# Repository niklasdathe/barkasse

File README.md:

# Barkasse Sensor Infrastructure

A simple, easy-to-extend sensor for the Barkasse project.

## 1. Hub

This section describes the setup and structure of the on board hub.

### 1.1 Core Ideas
- Sensor nodes (ESP32/Arduino) publish JSON over MQTT via Ethernet/PoE or WiFi.
- A Raspberry Pi / reTerminal acts as a central hub with Mosquitto + Node-RED (HTTP/WebSocket) serving a static UI.
- The UI auto-discovers new sensors and displays them live on a 10-inch touch panel.

### 1.2 MQTT Topics & JSON Schema
- Topic: `barkasse/<node>/<cluster>/<sensor>`
- Payload:
  ```json
  {
  "node": "esp32p4-01",
  "cluster": "weather",
  "sensor": "temperature",
  "value": 22.4,
  "unit": "°C",
  "ts": "2025-10-10T12:00:00Z"
  }
  ```
### 1.3 Directory Overview

| Folder                  | Description                                            |
| ----------------------- | ------------------------------------------------------ |
| `example-sensor-implementations/esp32p4-weatherstation-mock`  | ESP32-P4 (Ethernet) demo publishing weather data |
| `example-sensor-implementations/esp32-wroom-waterstation-mock`| ESP32 WROOM (WiFi) demo publishing water data    |
| `mosquitto/`            | Mosquitto config for native install                    |
| `nodered_data/`         | Node-RED userDir (flows + settings)                    |
| `ui/`                   | Static touchscreen UI                                  |
| `systemd/`              | System services for hub + fullscreen UI                |

### 1.4 Setup on Raspberry Pi

This repo is designed to run **without Docker**.

**1. Install Mosquitto + Node-RED**
```bash
sudo apt update
sudo apt install -y mosquitto mosquitto-clients
```

Install Node-RED (if not already present):
```bash
bash <(curl -sL https://raw.githubusercontent.com/node-red/linux-installers/master/deb/update-nodejs-and-nodered)
```

**2. Configure Mosquitto**
```bash
sudo cp mosquitto/mosquitto.conf /etc/mosquitto/conf.d/barkasse.conf
sudo systemctl enable --now mosquitto
```

**3. Enable services**
```bash
sudo cp systemd/barkasse-ui.service /etc/systemd/system/
sudo systemctl daemon-reload
sudo systemctl enable --now barkasse-ui.service
```

The UI is served at http://localhost:8080.

### 1.5 Isolated LAN (hub assigns IPs + NTP)

If the hub and ESP32 are the only devices on a switch, the hub must provide IP addresses.

This repo includes a small coordinator setup that configures:

- Static IP on `eth0` (default `192.168.10.10/24`)
- DHCP (dnsmasq) so the ESP32 gets an IP when plugged in
- NTP (chrony) served by the hub

Run:

```bash
chmod +x scripts/setup-lan-coordinator.sh scripts/barkasse-dhcp-mqtt-hook.sh
BARKASSE_LAN_IFACE=eth0 BARKASSE_LAN_IP=192.168.10.10 ./scripts/setup-lan-coordinator.sh
```

Details: see [docs/lan_coordinator.md](docs/lan_coordinator.md).

### 1.5 Implementation Examples

- **ESP32-P4 Weather (Ethernet)** (See `example-sensor-implementations/esp32p4-weatherstation-mock`)

- **ESP32 WROOM Water (WiFi)** (See `example-sensor-implementations/esp32-wroom-waterstation-mock`)

- **(LoRa)** TODO

### 1.6 Extend
Add any new sensor/cluster by publishing to the topic contract. No UI edits required.

### 1.7 Maintenance

- Check backend: systemctl status barkasse-ui.service
- Check browser: systemctl status barkasse-fullscreen.service
- Update manually: git pull && sudo systemctl restart barkasse-ui barkasse-fullscreen

### 1.8 UI menu (clear history & fullscreen)

The hub keeps recent datapoints in memory to render charts. You can delete this local history if needed:

- UI: Use the top-right menu (⋮) and choose "Clear history". All stored series are removed.
- API: Send a POST request to the hub:
  - Clear everything: POST /history/clear
  - Clear one series: POST /history/clear?key=<node>/<cluster>/<sensor>

This only affects the in-memory cache on the Pi; live updates continue as new datapoints arrive.

This setup does not require Chromium at all. If you want the UI to open automatically on boot
in fullscreen, enable `systemd/barkasse-fullscreen.service`.

## 2. Server

This section describes the setup and structure of the server side.  

| MQTT topic (barkasse/node)                               | node         | cluster     | sensor                 | unit     | What it means                                                                      | Source / where it comes from                                                |
| ----------------------------------------- | ------------ | ----------- | ---------------------- | -------- | ---------------------------------------------------------------------------------- | --------------------------------------------------------------------------- |
| `barkasse/esp32p4-01` | `esp32p4-01` | `weather`   | `temperature`          | `°C`     | Ambient/outside temperature (mock)                                                 | ESP32-P4 weather mock (`publishSensor("temperature", ...)`)                 |
| `barkasse/esp32p4-01`    | `esp32p4-01` | `weather`   | `humidity`             | `%`      | Relative humidity (mock)                                                           | ESP32-P4 weather mock                                                       |
| `barkasse/esp32p4-01`    | `esp32p4-01` | `weather`   | `pressure`             | `hPa`    | Air pressure (mock)                                                                | ESP32-P4 weather mock                                                       |
| `barkasse/esp32p4-01`  | `esp32p4-01` | `weather`   | `wind_speed`           | `m/s`    | Wind speed (mock)                                                                  | ESP32-P4 weather mock                                                       |
| `barkasse/esp32p4-01`    | `esp32p4-01` | `weather`   | `wind_dir`             | `°`      | Wind direction (0–360°) (mock)                                                     | ESP32-P4 weather mock                                                       |
| `barkasse/esp32p4-01`       | `esp32p4-01` | `weather`   | *(summary envelope)*   | —        | One JSON message containing **all weather sensors** under `sensors{...}`           | ESP32-P4 weather mock (`publishCluster()`)                                  |
| `barkasse/sensors`                        | `hub`        | `enclosure` | `temperature`          | `°C`     | Enclosure internal air temperature                                                 | Hub I2C script AM2301B (`am2301b_read.py` → MQTT Publish Enclosure)         |
| `barkasse/sensors`                        | `hub`        | `enclosure` | `humidity`             | `%`      | Enclosure internal relative humidity                                               | Hub I2C script AM2301B (`am2301b_read.py` → MQTT Publish Enclosure)         |
| `barkasse/sensors`                        | `hub`        | `enclosure` | `surface_temp`         | `°C`     | Estimated “cold surface” temperature inside enclosure (used for condensation risk) | Node-RED “Condensation Risk” flow: `T_surface = (T_inside + T_outside)/2`   |
| `barkasse/sensors`                        | `hub`        | `enclosure` | `dew_point`            | `°C`     | Dew point temperature computed from inside T + RH (Magnus formula)                 | Node-RED “Condensation Risk” flow                                           |
| `barkasse/sensors`                        | `hub`        | `enclosure` | `condensation_delta`   | `°C`     | `dew_point - surface_temp` (positive ⇒ condensation likely)                        | Node-RED “Condensation Risk” flow                                           |
| `barkasse/sensors`                        | `hub`        | `enclosure` | `condensation_risk`    | `%`      | Risk mapped from `condensation_delta` using linear low/high thresholds             | Node-RED “Condensation Risk” flow (`risk_low_delta_c`, `risk_high_delta_c`) |
| `barkasse/sensors`                        | `hub`        | `enclosure` | `condensation`         | *(none)* | Boolean flag: `1` if `surface_temp <= dew_point`, else `0`                         | Node-RED “Condensation Risk” flow                                           |
| `barkasse/sensors`                        | `hub`        | `gnss`      | `fix_valid`            | *(none)* | RMC validity (A=1 / V=0)                                                           | Node-RED GNSS parser (EC25 NMEA → JSON)                                     |
| `barkasse/sensors`                        | `hub`        | `gnss`      | `fix_quality`          | *(none)* | GGA fix quality (0=no fix, 1=GPS, 2=DGPS, …)                                       | Node-RED GNSS parser (from GGA)                                             |
| `barkasse/sensors`                        | `hub`        | `gnss`      | `fix_type`             | *(none)* | GSA fix type (1=no fix, 2=2D, 3=3D)                                                | Node-RED GNSS parser (from GSA)                                             |
| `barkasse/sensors`                        | `hub`        | `gnss`      | `sats_used`            | *(none)* | Satellites used in solution                                                        | Node-RED GNSS parser (from GGA)                                             |
| `barkasse/sensors`                        | `hub`        | `gnss`      | `hdop`                 | *(none)* | Horizontal dilution of precision                                                   | Node-RED GNSS parser (GGA/GSA)                                              |
| `barkasse/sensors`                        | `hub`        | `gnss`      | `pdop`                 | *(none)* | Position dilution of precision                                                     | Node-RED GNSS parser (from GSA)                                             |
| `barkasse/sensors`                        | `hub`        | `gnss`      | `vdop`                 | *(none)* | Vertical dilution of precision                                                     | Node-RED GNSS parser (from GSA)                                             |
| `barkasse/sensors`                        | `hub`        | `gnss`      | `lat`                  | `deg`    | Latitude in decimal degrees                                                        | Node-RED GNSS parser (RMC/GGA)                                              |
| `barkasse/sensors`                        | `hub`        | `gnss`      | `lon`                  | `deg`    | Longitude in decimal degrees                                                       | Node-RED GNSS parser (RMC/GGA)                                              |
| `barkasse/sensors`                        | `hub`        | `gnss`      | `alt`                  | `m`      | Altitude above mean sea level                                                      | Node-RED GNSS parser (from GGA)                                             |
| `barkasse/sensors`                        | `hub`        | `gnss`      | `speed`                | `m/s`    | Ground speed (converted from knots if needed)                                      | Node-RED GNSS parser (RMC/VTG)                                              |
| `barkasse/sensors`                        | `hub`        | `gnss`      | `speed_kmh`            | `km/h`   | Ground speed in km/h                                                               | Node-RED GNSS parser (RMC/VTG)                                              |
| `barkasse/sensors`                        | `hub`        | `gnss`      | `course`               | `deg`    | Course over ground                                                                 | Node-RED GNSS parser (RMC/VTG)                                              |
| `barkasse/sensors`                        | `hub`        | `gnss`      | `gps_sats_in_view`     | *(none)* | GPS satellites in view (from GSV aggregation)                                      | Node-RED GNSS parser (GSV cycle)                                            |
| `barkasse/sensors`                        | `hub`        | `gnss`      | `gps_snr_avg`          | `dB`     | Average SNR of GPS sats in view                                                    | Node-RED GNSS parser (GSV cycle)                                            |
| `barkasse/sensors`                        | `hub`        | `gnss`      | `galileo_sats_in_view` | *(none)* | Galileo satellites in view (from GSV aggregation)                                  | Node-RED GNSS parser (GSV cycle)                                            |
| `barkasse/sensors`                        | `hub`        | `gnss`      | `galileo_snr_avg`      | `dB`     | Average SNR of Galileo sats in view                                                | Node-RED GNSS parser (GSV cycle)                                            |

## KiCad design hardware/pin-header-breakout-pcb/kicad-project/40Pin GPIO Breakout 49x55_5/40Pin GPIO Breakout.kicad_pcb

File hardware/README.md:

This folder holds the informations / files for the hardware components of the hub.

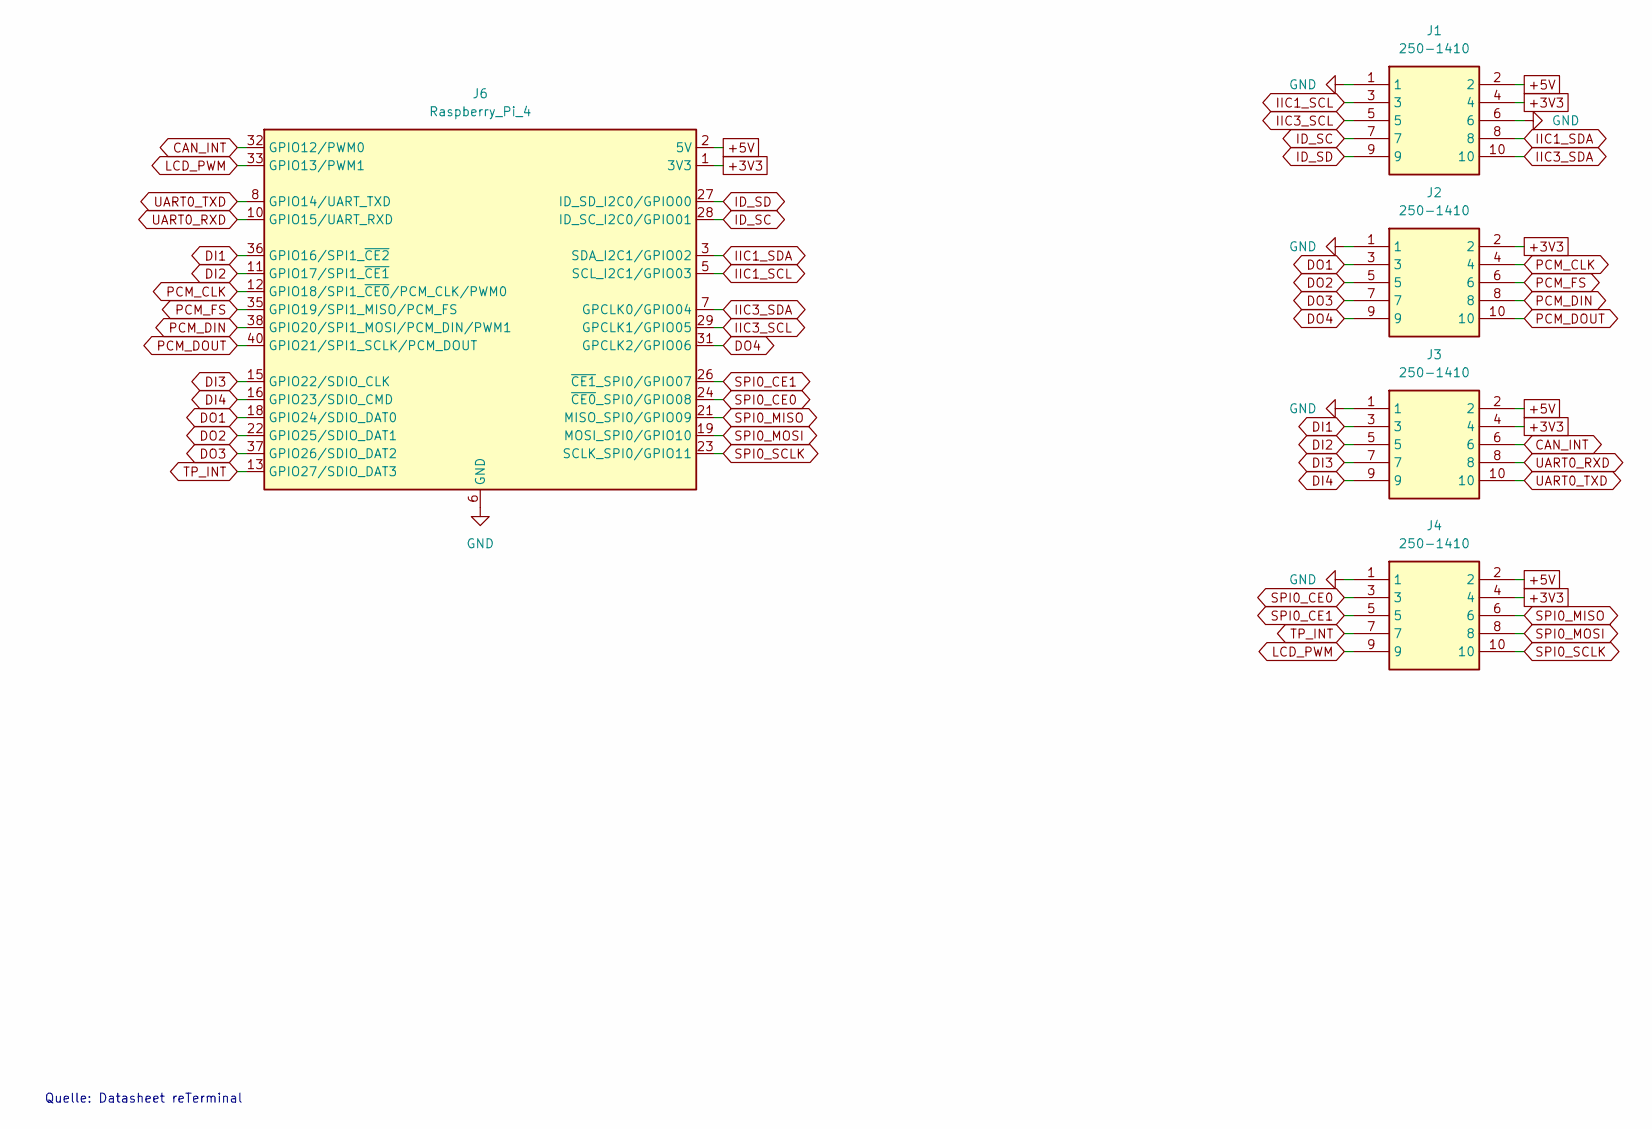
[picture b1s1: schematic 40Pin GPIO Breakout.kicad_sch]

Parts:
J1, J2, J3, J4: 250-1410; CONN10_250-1410_WAG; Manufacturer_Part_Number 250-1410
J6: Raspberry_Pi_4; PinHeader_2x20_P2.54mm_Vertical

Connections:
+3V3: J1.4, J2.2, J3.4, J4.4, J6.1 (3V3), J6.17 (3V3)
+5V: J1.2, J3.2, J4.2, J6.2 (5V), J6.4 (5V)
CAN_INT: J3.6, J6.32 (GPIO12/PWM0)
DI1: J3.3, J6.36 (GPIO16/SPI1_~CE2)
DI2: J3.5, J6.11 (GPIO17/SPI1_~CE1)
DI3: J3.7, J6.15 (GPIO22/SDIO_CLK)
DI4: J3.9, J6.16 (GPIO23/SDIO_CMD)
DO1: J2.3, J6.18 (GPIO24/SDIO_DAT0)
DO2: J2.5, J6.22 (GPIO25/SDIO_DAT1)
DO3: J2.7, J6.37 (GPIO26/SDIO_DAT2)
DO4: J2.9, J6.31 (GPCLK2/GPIO06)
GND: J1.1, J1.6, J2.1, J3.1, J4.1, J6.6 (GND), J6.9 (GND), J6.14 (GND), J6.20 (GND), J6.25 (GND), J6.30 (GND), J6.34 (GND), J6.39 (GND)
ID_SC: J1.7, J6.28 (ID_SC_I2C0/GPIO01)
ID_SD: J1.9, J6.27 (ID_SD_I2C0/GPIO00)
IIC1_SCL: J1.3, J6.5 (SCL_I2C1/GPIO03)
IIC1_SDA: J1.8, J6.3 (SDA_I2C1/GPIO02)
IIC3_SCL: J1.5, J6.29 (GPCLK1/GPIO05)
IIC3_SDA: J1.10, J6.7 (GPCLK0/GPIO04)
LCD_PWM: J4.9, J6.33 (GPIO13/PWM1)
PCM_CLK: J2.4, J6.12 (GPIO18/SPI1_~CE0/PCM_CLK/PWM0)
PCM_DIN: J2.8, J6.38 (GPIO20/SPI1_MOSI/PCM_DIN/PWM1)
PCM_DOUT: J2.10, J6.40 (GPIO21/SPI1_SCLK/PCM_DOUT)
PCM_FS: J2.6, J6.35 (GPIO19/SPI1_MISO/PCM_FS)
SPI0_CE0: J4.3, J6.24 (~CE0_SPI0/GPIO08)
SPI0_CE1: J4.5, J6.26 (~CE1_SPI0/GPIO07)
SPI0_MISO: J4.6, J6.21 (MISO_SPI0/GPIO09)
SPI0_MOSI: J4.8, J6.19 (MOSI_SPI0/GPIO10)
SPI0_SCLK: J4.10, J6.23 (SCLK_SPI0/GPIO11)
TP_INT: J4.7, J6.13 (GPIO27/SDIO_DAT3)
UART0_RXD: J3.8, J6.10 (GPIO15/UART_RXD)
UART0_TXD: J3.10, J6.8 (GPIO14/UART_TXD)

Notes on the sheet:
Quelle: Datasheet reTerminal

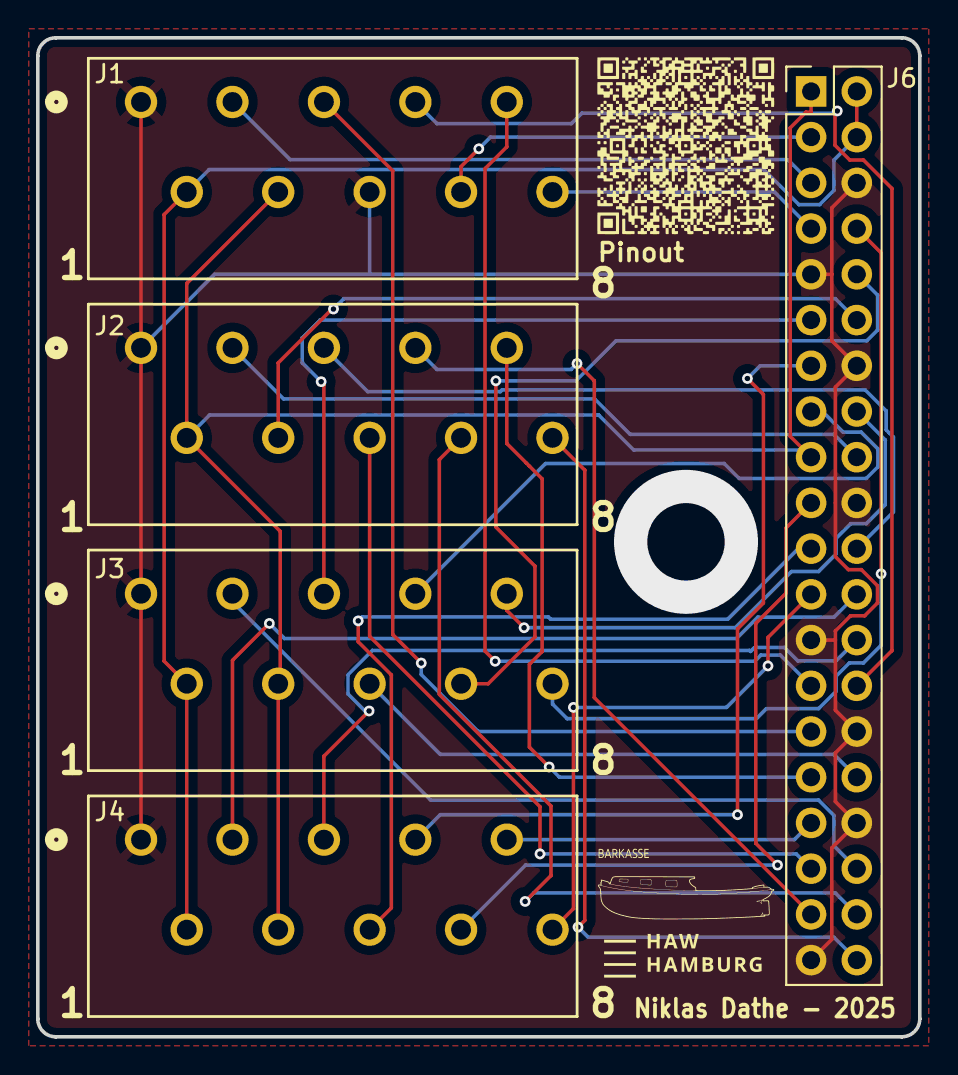
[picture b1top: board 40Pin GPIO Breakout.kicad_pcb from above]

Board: 2 copper layers, 49.0 x 55.5 mm, 5 parts (0 on the bottom side), 31 nets.

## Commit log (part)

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2025-10-09 Implement weather cluster emulation with MQTT
    This code emulates a weather cluster using an ESP32-P4, publishing temperature, humidity, pressure, and wind data via MQTT. It includes setup for Ethernet connectivity and JSON serialization for sens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
2025-10-09 Add Mosquitto configuration file
2025-10-09 Add FastAPI, Uvicorn, and Paho-MQTT dependencies
2025-10-09 Implement FastAPI with MQTT integration
2025-10-09 Add initial HTML structure for Barkasse Hub
2025-10-09 Add styles for layout and design in styles.css
2025-10-09 Rename pi/app/background.png to pi/app/static/background.png
2025-10-09 Revise README for folder structure and UI instructions
    Updated folder names and simplified UI startup instructions.
2025-10-09 Add systemd service for Chromium kiosk mode
2025-10-10 functioning commuication
2025-10-10 added aüpp.js with tile system
2025-10-10 Update styles.css
    Moved the tiles to reveal the subtitle of the background picture
2025-10-10 Increase top padding of main grid
2025-10-10 Add auto-git-update.service for automatic updates
    This service automatically updates the Barkasse project from GitHub when the network is online.
2025-10-10 Update service description and dependencies
2025-10-10 Relocate auto-git-update.service file
    Move auto-git-update.service to /etc/systemd/system.
2025-10-10 Refactor kiosk-chromium.service configuration
    Moved service file to /etc/systemd/system and updated ExecStart options for Chromium.
2025-10-10 Change service user and working directory for barkasse-ui
2025-10-10 Change user and update git pull logic in service
2025-10-10 Modify barkasse-ui.service for better execution
    Updated service file to run uvicorn with virtual environment activation and added group specification.
2025-10-10 Modify kiosk-chromium.service for Wayland and user settings
    Updated kiosk-chromium.service for Wayland support and improved environment variables.
2025-10-10 Update header to include 'DASHBOARD'
2025-10-10 Change title from 'BARKASSE DASHBOARD' to 'SENSOR-HUB'
2025-10-10 Enable drag-and-drop reordering for dashboard tiles
2025-10-10 Improve tile drag animations
2025-10-10 Revert "Improve tile drag animations"
2025-10-10 Revise README for clarity and additional details
    Updated README to enhance clarity and structure, including MQTT topics and JSON schema.
2025-10-10 Add maintenance section to README
    Added maintenance section with service checks and update instructions.
2025-10-10 Refactor app.js for tile management and charts
    Refactor app.js to enhance tile management and chart functionality. Added drag-and-drop support for tiles, improved WebSocket handling, and updated chart rendering logic.
2025-10-10 Enhance styles for layout and components
    Added styles for header, periods, chart section, and tile elements.
2025-10-10 Update index.html structure and add chart section
2025-10-10 Reorganize HTML structure for chart and tiles
2025-10-10 Enable droppable functionality for trash element
    Updated styles for the trash element to allow droppable functionality when visible.
2025-10-10 Enhance chart rendering and title management
    Updated chart rendering logic to handle cases with no data and improved chart title/hint management.
2025-10-10 Refactor timestamp handling and improve comments
2025-10-10 Reorganize HTML structure for better layout
2025-10-10 Refactor styles for layout and components
2025-10-10 Refactor app.js for improved readability and performance
    Refactor and optimize JavaScript code for better readability and performance. Includes improvements in WebSocket handling, tile rendering, and timestamp parsing.
2025-10-10 Refactor timestamp handling and update health dot logic
2025-10-10 Refactor periods styles and button appearance
    Updated styles for the periods class and buttons.
2025-10-10 Refactor cutoff logic and data initialization
2025-10-10 Refactor app.js for clarity and efficiency
    Refactor app.js to improve readability and maintainability by reorganizing functions, removing redundant code, and updating variable names.
2025-10-10 Refactor main.py for improved readability and structure
2025-10-10 Enhance timestamp handling in main.py for better accuracy and readability. Improved normalization logic for various timestamp formats and added fallback to current time on parsing failure.
2025-10-10 Implement NTP synchronization and time validation in main.ino. Added functions to check time validity and synchronize time via SNTP, ensuring accurate timestamps for data publishing.
2025-10-13 Refactor styles for header and chart tiles
2025-10-13 Refactor app.js to include HTML layout
    Replaced JavaScript code with HTML structure for the app.
2025-10-13 Refactor app.js to include helper functions and globals
2025-10-13 Add HTML structure for Barkasse Hub
2025-10-13 Enhance styles for floating action buttons and layout
    Added transition effects to floating action buttons and improved layout styles.
2025-10-13 Refactor app.js for improved readability and structure
2025-10-13 Refactor chart handling and drag-and-drop features
    Refactor chart handling and drag-and-drop functionality in app.js. Updated event listeners and improved chart rendering logic.
2025-10-13 Refactor index.html structure and remove duplicates
2025-10-13 Refactor styles for grid and button elements
2025-10-13 Add HTML structure and metadata to index.html
2025-10-13 Embed chart tile in grid and add graph creation dropzone
2025-10-13 Allow multiple concurrent graph tiles
2025-10-13 Revert "Allow multiple graphs and enforce half-width layout"
2025-10-13 Refactor graph tile logic for multi-instance support
    Refactor graph tile handling to support multiple instances and improve event management.
2025-10-13 Implement responsive grid layout for main section
    Added responsive grid layout for sensors and adjusted graph tile spans.
2025-10-13 Add graph placeholder tile to index.html
    Added optional placeholder for graph on initial load.
2025-10-13 Enhance canvas resizing and drag-and-drop functionality
    Added canvas resizing to match tile size and prevent blur. Improved drag-and-drop event handling and error management for data fetching.
2025-10-14 Refactor grid layout and tile dimensions in CSS
2025-10-14 Implement drag-and-drop with placeholders
    Added drag-and-drop functionality with placeholder support.
2025-10-14 Refactor CSS for layout and styling improvements
2025-10-14 Refactor app.js for topic tiles and drag-and-drop
    Refactor app.js to support topic tiles and improve drag-and-drop functionality. Removed unused functions and adjusted event handlers for better performance.
2025-10-14 Enhance index.html with graph sections and utilities
    Added new graph sections and utility drop zones.
2025-10-14 Refactor index.html structure and add metadata
2025-10-14 Refactor CSS for improved layout and spacing
    Updated styles for header, topics, and graphs layout. Adjusted padding, margins, and display properties for improved spacing and responsiveness.
2025-10-14 Refactor CSS for improved readability and consistency
2025-10-14 Enhance tile creation and drag functionality
    Refactor tile creation and drag handling for better touch support.
2025-10-14 Refactor CSS with variables for easier customization
2025-10-14 Modify scrollbar width and comments in styles.css
    Updated scrollbar width for better visibility and adjusted comments for clarity.
2025-10-14 Refactor CSS variables and layout styles
2025-10-14 Increase scrollbar thickness and padding values
2025-10-14 Adjust CSS variables and layout properties
2025-10-14 Adjust padding-bottom for scrollbar spacing
    Increased padding-bottom to provide more breathing room for the scrollbar.
2025-10-14 Increase horizontal padding around content
2025-10-14 Align drag image with pointer
2025-11-29 Force sync local state to remote / Refactoring to using NodeRED backend
2025-11-29 Zwischenstand rm /static/
2025-11-29 added flow
2025-11-30 Refactor app.js to enhance structure and readability; added detailed comments and documentation for global variables, helper functions, and WebSocket handling. Improved drag-and-drop functionality fo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
2025-12-02 Add "Clear history" functionality to the UI and backend
    - Introduced a button in the UI to clear local history of sensor data.
    - Implemented backend API endpoint to handle history clearing requests.
    - Updated styles for the new button and adjusted layout for better alignment.
    - Added confirmation prompt before clearing history to prevent accidental deletions.
2025-12-02 Add context menu for tiles with "Clear history" action and long-press support
2025-12-02 Add actions button to tiles for enhanced interaction; update styles for positioning
2025-12-02 Refactor CSS variables and comments for improved clarity and maintainability; adjust styles for better layout and visual consistency
2025-12-02 Fix positioning of the dot in tile component for improved visual alignment
2025-12-02 Adjust positioning of the dot in tile component for improved visual alignment
2025-12-02 Add Plymouth theme and script for branded boot splash
2025-12-02 Implement header menu with clear history and kiosk mode options
2025-12-02 Add kiosk mode toggle functionality and related UI updates
2025-12-02 Refactor header menu to consolidate clear history and fullscreen toggle functionality; update kiosk mode handling in UI and backend integration.
2025-12-08 Add TODO and feature ideas for power management
2025-12-09 Add thesis topic and feature ideas to TODO.md
2025-12-21 Add Hardware Watchdog to TODO list
2025-12-22 Add LTE Tailscale setup documentation
    This document outlines the configuration and setup for the Barkasse hub using the Quectel EC25 modem with NetworkManager and Tailscale, including troubleshooting tips and key concepts.
2025-12-22 Create time_sync.md for Barkasse hub configuration
    Added comprehensive documentation for setting up reliable time synchronization using RTC, chrony NTP server, and nftables on the Barkasse hub. Includes system context, goals, architecture, configurat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
2025-12-22 Rename LTE_tailscale.md to lte_tailscale.md
2025-12-30 Add task to check external antenna on CM4
2026-01-02 Add README for hardware components
2026-01-02 Create temp
2026-01-21 Sync local folder structure and content to repository
2026-01-22 Added table explaining topics currently being published
2026-01-22 Refactor graph rendering methods for performance.
2026-01-22 Add tooltip functionality to GraphTile for enhanced data visualization
2026-01-22 Add refresh page option to header menu giving f5 functionality
2026-02-04 Enhance touch drag functionality with improved event handling and overlay management
2026-02-04 Remove scroll snapping from header and tile elements for improved layout flexibility
2026-02-09 Add manual input modal for user-defined sensor values
2026-02-09 Refactor header menu button styles for improved alignment and appearance
2026-02-11 feat: Enhance security and persistence for Barkasse Hub
    - Updated Mosquitto configuration to disable anonymous access and enable password authentication with TLS support.
    - Modified systemd service for Chromium to wait for the UI backend on HTTPS and added crash recovery for seamless user experience.
    - Adjusted Node-RED service to ensure proper directory structure for user data.
    - Improved touch drag performance in UI by caching drop targets.
    - Reduced CSS shadow effects and removed performance-heavy filters for better UI responsiveness.
    - Added comprehensive documentation on security measures and persistent data storage for InfluxDB and MQTT.
2026-02-14 Add comprehensive UI styling documentation for Barkasse Hub
    - Introduced a new markdown file detailing CSS custom properties for theming.
    - Documented layout system using flexbox and grid for dashboard components.
    - Provided styling guidelines for tiles, graphs, and modals.
    - Included scrollbar customization and performance optimization strategies.
    - Added sections on touch and kiosk optimizations, along with theming instructions.
